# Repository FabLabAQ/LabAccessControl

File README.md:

# LabAccessControl

## FabLab access and machine control system proof-of-concept
* We use this system to manage access to our laboratory and machines usage (3D printers, laser cutter, CNC mill, etc.).
* Maker friendly and customizable, based on ESP8266 and programmed through the Arduino IDE.
* The ESP retrieves an authorized RFID cards list from a Google sheet and stores that list on flash memory, only when that list changes the internal cards list is updated with minimum flash memory wearing.
* It also logs events (what happened, when, and eventually who) on an internal FIFO and sends these logs to another Google sheet when internet connection is available.
* Due to the features above, this system can work also when internet connection goes down.

# WARNING:
Don't use MIFARE Classic cards if you don't want unauthorized access, they are clonable. Use at least Ultralight C for secure encryption.

# Development
## TODO (urgent)
Common
- [ ] diversify card keys
- [ ] switch to msgpack instead of json

Firmware
- [ ] replace DES library
- [ ] implement DES key generation
- [ ] switch to incremental mode for db updates
- [ ] implement signed messages
- [ ] implement provisioning and recovery of keys (Tang-like)

Script
- [ ] unify sheets
- [ ] incremental updates
- [ ] provisioning and recovery

App
- [ ] signed messages

## Wishlist
- [ ] switch to MQTT
- [ ] full server implmentation
- [ ] code refactoring
- [ ] external crypto chip
- [ ] smartphone nfc auth

Notes:

External crypto chip: should be used to generate card keys through hkdf/hmac, holding the source key securely and allowing it to be used only on successful authentication by the host MCU. The MCU should authenticate by recovering its private key using the procedure described above (Tang-like) or should use encrypted communications with that key.

Smartphone nfc auth: without changing the nfc reader chip (RC522), the only usable mode is host card emulation, which doesn't have a fixed UID, so the authentication protocol must be implemented on top of NDEF messages. For example: first the reader determines it's a smartphone, eventually by reading the ndef message from it, then begins the authentication process in which the reader, writing an NDEF message to the smartphone's emulated card, asks to hash some random data, and once hashed/signed using the phone's private key, that data should be read through another NDEF message and verified using the public key on the reader.

HTTP requests from Android: try retrofit

Test key: `KhGJGmHMHDS0FubbcqiVnAqxoRv1SlqD0Mg/EtXrdb0=`

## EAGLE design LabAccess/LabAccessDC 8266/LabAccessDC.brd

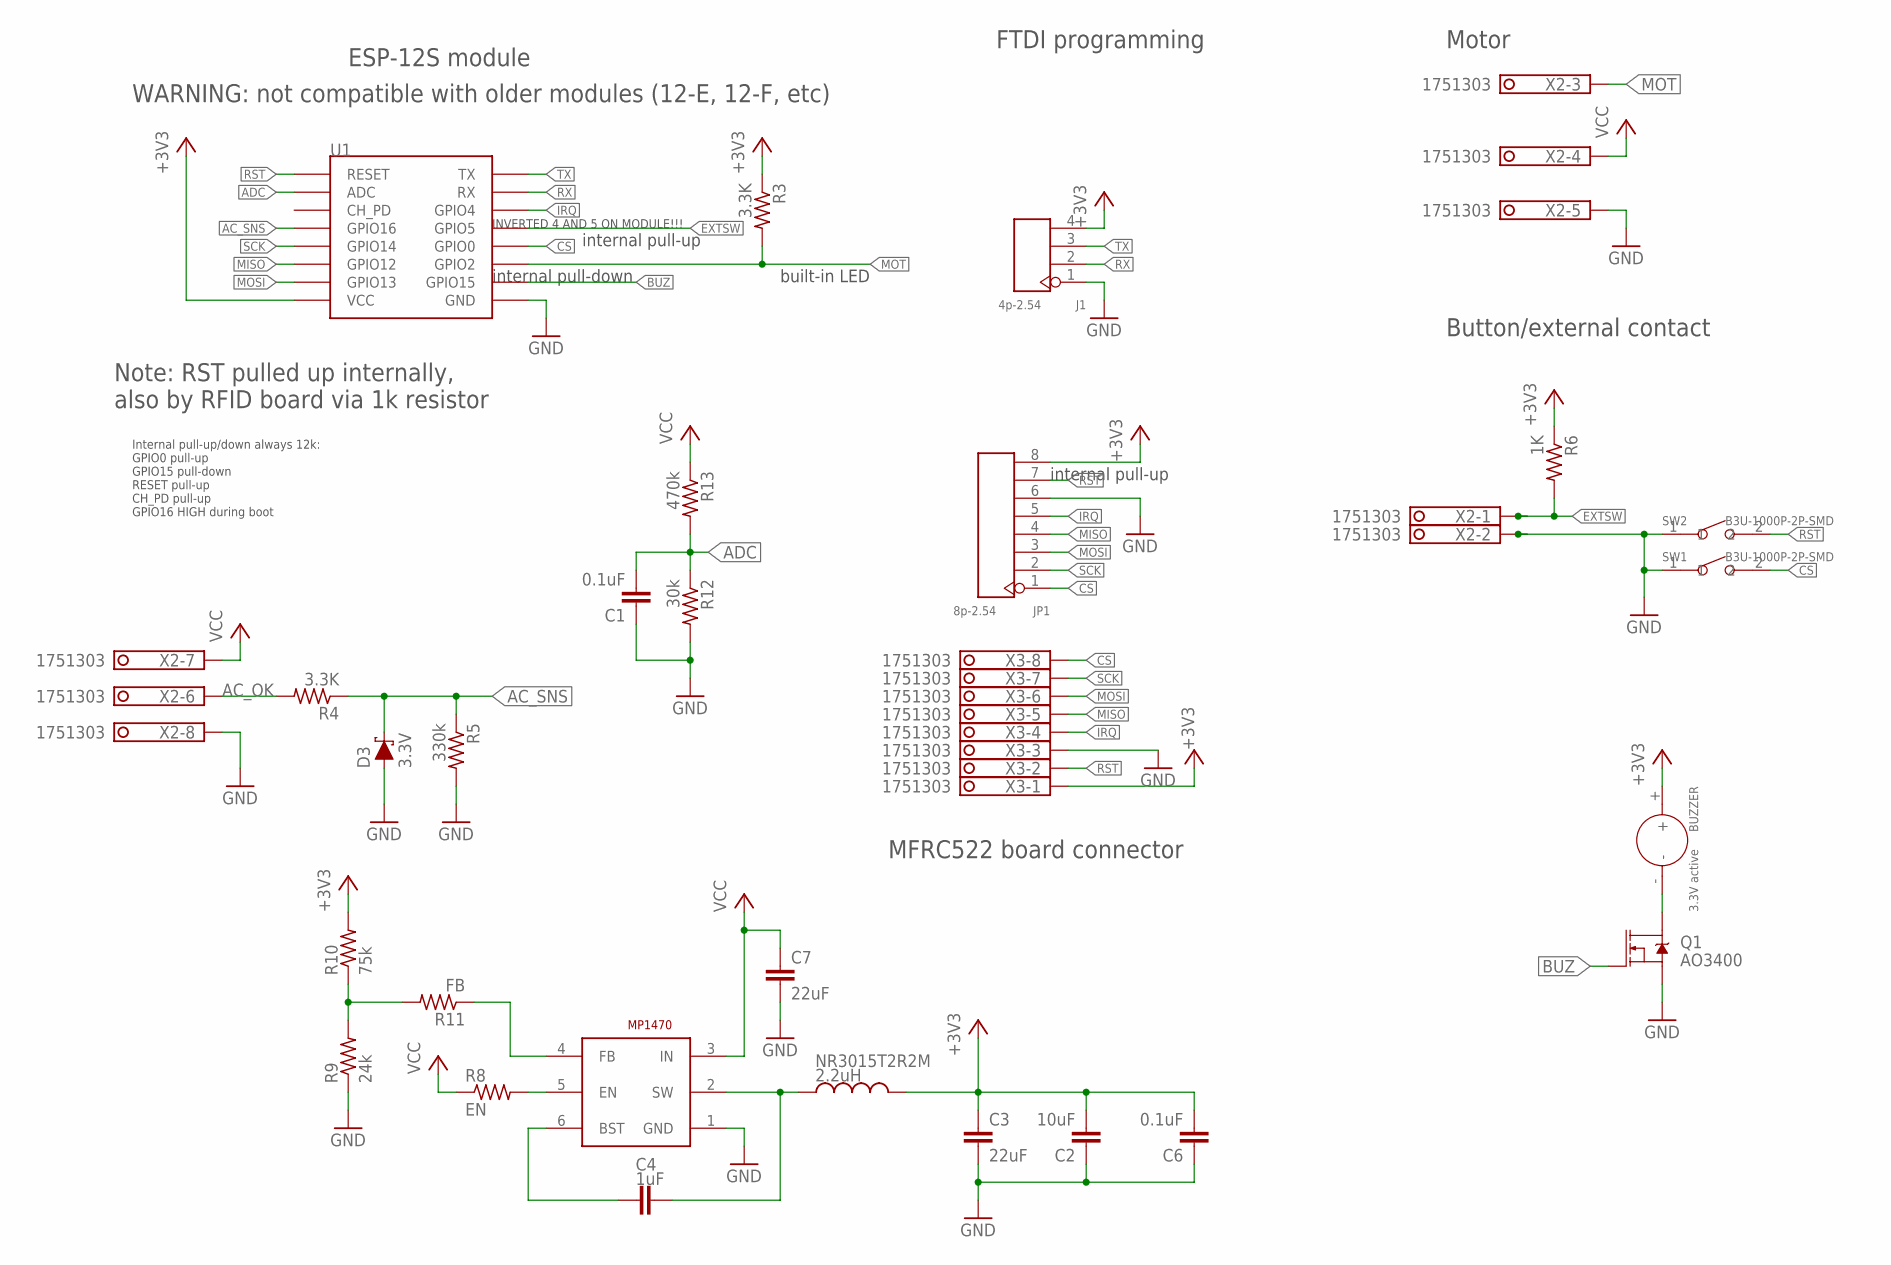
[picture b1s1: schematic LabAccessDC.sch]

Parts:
BUZZER: 3.3V active; BZ2-7.6-D12.0XH6.5MM
C1, C6: 0.1uF; C0603K
C2: 10uF; C0805K
C3, C7: 22uF; C0805K
C4: 1uF; C0603K
D3: 3.3V; SPARKFUN-DISCRETESEMI_SOD-523
J1: 4p-2.54; H4-2.54
JP1: 8p-2.54; H8-2.54
MP1470: MP1470GJ; TSOT-23-6
NR3015T2R2M: 2.2uH; INDUCTOR-NR3015
Q1: AO3400; SOT23-3
R3, R4: 3.3K; R0603
R5: 330k; R0603
R6: 1K; R0603
R8: EN; R0603
R9: 24k; R0603
R10: 75k; R0603
R11: FB; R0603
R12: 30k; R0603
R13: 470k; R0603
SW1, SW2: B3U-1000P-2P-SMD; SW2-2.6-3.0X2.5X1.2+0.4MM
U1: ESP12SMD; ESP12-SMD
X2, X3: 1751303

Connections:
+3V3: BUZZER.+, C2.2, C3.1, C6.2, J1.4, JP1.8, NR3015T2R2M.2, R3.1, R6.1, R10.2, U1.VCC, X3.1
AC_OK: R4.2, X2.6
AC_SNS: D3.C, R4.1, R5.1, U1.GPIO16
ADC: C1.2, R12.1, R13.2, U1.ADC
BUZ: Q1.1 (G), U1.GPIO15
CS: JP1.1, SW1.2, U1.GPIO0, X3.8
EXTSW: R6.2, U1.GPIO5, X2.1
GND: C1.1, C2.1, C3.2, C6.1, C7.2, D3.A, J1.1, JP1.6, MP1470.1 (GND), Q1.2 (S), R5.2, R9.1, R12.2, SW1.1, SW2.1, U1.GND, X2.2, X2.5, X2.8, X3.3
IRQ: JP1.5, U1.GPIO4, X3.4
MISO: JP1.4, U1.GPIO12, X3.5
MOSI: JP1.3, U1.GPIO13, X3.6
MOT: R3.2, U1.GPIO2, X2.3
unnamed: BUZZER.-, Q1.3 (D)
unnamed: C4.1, MP1470.6 (BST)
unnamed: C4.2, MP1470.2 (SW), NR3015T2R2M.1
unnamed: MP1470.5 (EN), R8.2
unnamed: R9.2, R10.1, R11.2
unnamed: MP1470.4 (FB), R11.1
RST: JP1.7, SW2.2, U1.RESET, X3.2
RX: J1.2, U1.RXD0 (RX)
SCK: JP1.2, U1.GPIO14, X3.7
TX: J1.3, U1.TXD0 (TX)
VCC: C7.1, MP1470.3 (IN), R8.1, R13.1, X2.4, X2.7

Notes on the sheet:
ESP-12S module
Note: RST pulled up internally, also by RFID board via 1k resistor
FTDI programming
Button/external contact
MFRC522 board connector
built-in LED
internal pull-down
internal pull-up
INVERTED 4 AND 5 ON MODULE!!!
Internal pull-up/down always 12k: GPIO0 pull-up GPIO15 pull-down RESET pull-up CH_PD pull-up GPIO16 HIGH during boot
Motor
WARNING: not compatible with older modules (12-E, 12-F, etc)

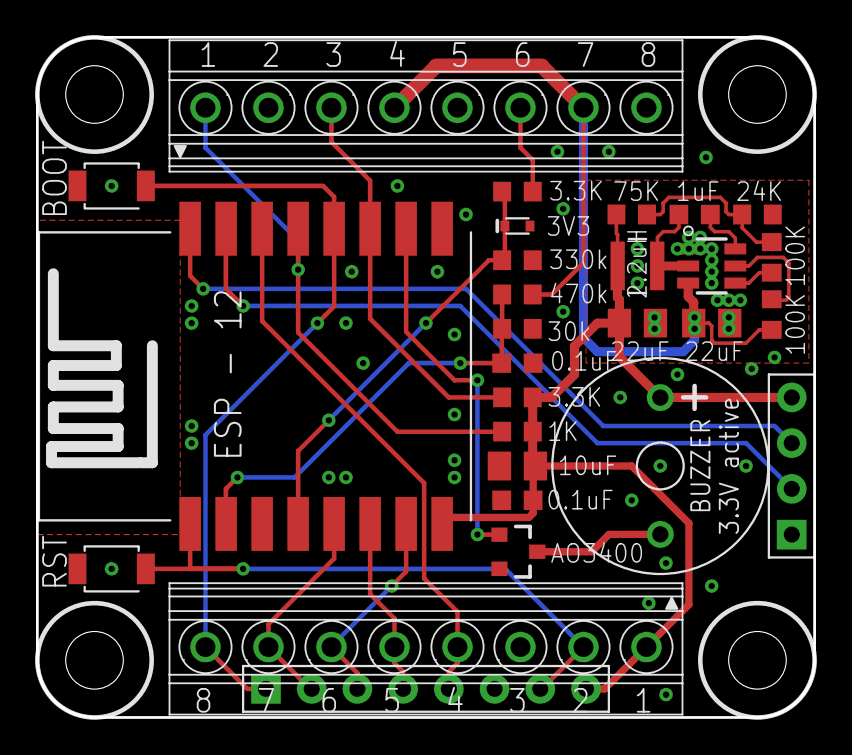
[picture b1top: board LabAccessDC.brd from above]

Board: 2 copper layers, 43.2 x 37.8 mm, 29 parts (1 on the bottom side), 23 nets.

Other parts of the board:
U$3: OSHW-LOGO-L

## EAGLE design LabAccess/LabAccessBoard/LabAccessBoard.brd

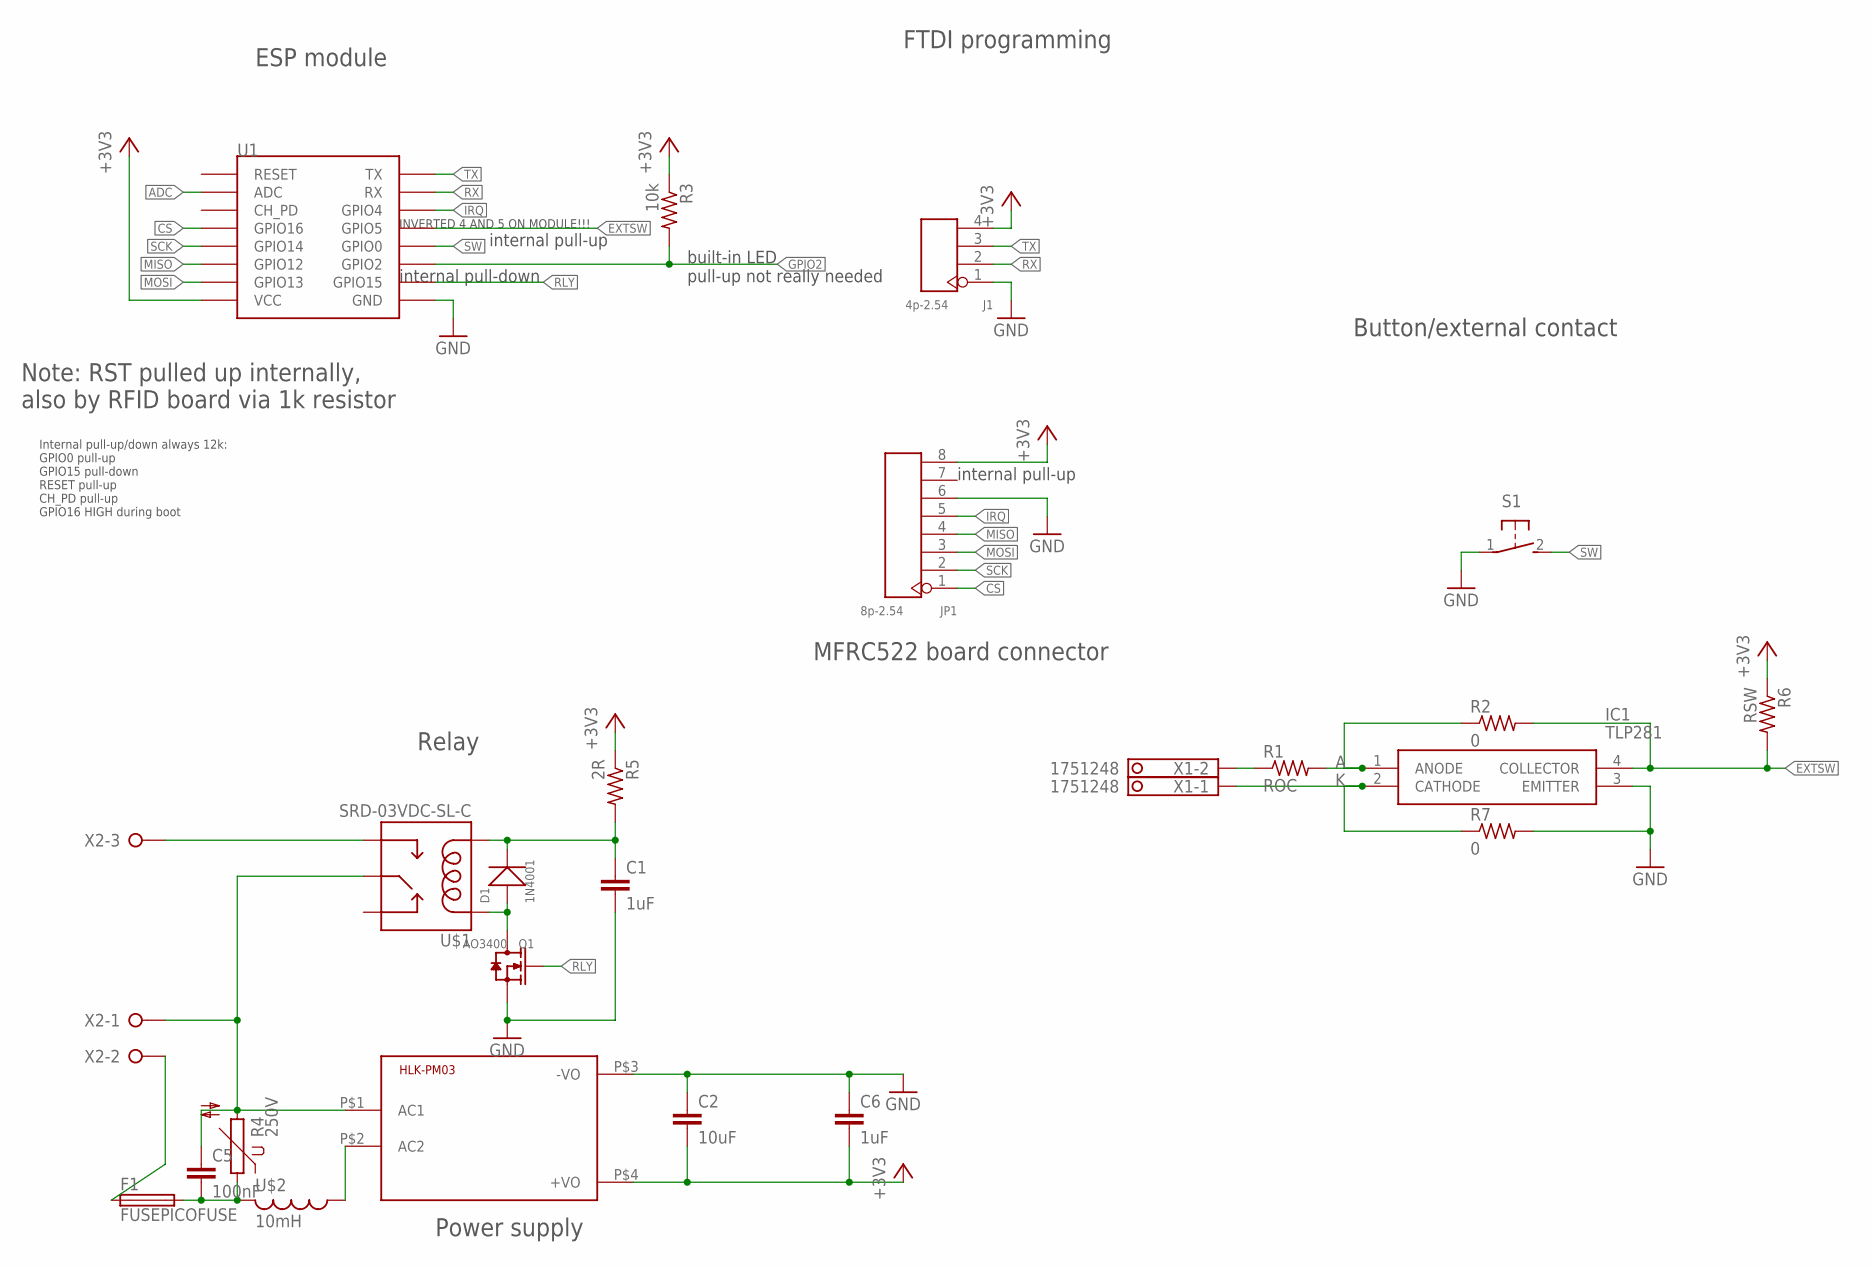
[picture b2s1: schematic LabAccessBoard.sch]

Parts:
C1, C6: 1uF; C0603K
C2: 10uF; C0805K
C5: 100nF; C102-064X133
D1: 1N4001; DO-214AC
F1: FUSEPICOFUSE; PICOFUSE
HLK-PM03: HLK-PM03; HLK-PM01
IC1: TLP281; SOIC127P700X190-4N
J1: 4p-2.54; H4-2.54
JP1: 8p-2.54; H8-2.54
Q1: AO3400; SOT-23
R1: ROC; R0603
R2, R7: 0; R0603
R3: 10k; R0603
R4: 250V; S07K250
R5: 2R; R0603
R6: RSW; R0603
S1: 31-XX; B3F-31XX
U1: ESP12SMD; ESP12-SMD
U$1: SRD-03VDC-SL-C; SRD-0XVDC-SL-C
U$2: 10mH; 6000-XXXX-RC
X1: 1751248
X2: W237-3E

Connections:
+3V3: C2.2, C6.2, HLK-PM03.P$4 (+VO), J1.4, JP1.8, R3.1, R5.1, R6.1, U1.VCC
A: IC1.1 (ANODE), R1.2, R2.1
ADC: U1.ADC
CS: JP1.1, U1.GPIO16
EXTSW: IC1.4 (COLLECTOR), R2.2, R6.2, U1.GPIO5
GND: C1.2, C2.1, C6.1, HLK-PM03.P$3 (-VO), IC1.3 (EMITTER), J1.1, JP1.6, Q1.2 (S), R7.2, S1.1, U1.GND
GPIO2: R3.2, U1.GPIO2
IRQ: JP1.5, U1.GPIO4
K: IC1.2 (CATHODE), R7.1, X1.1
MISO: JP1.4, U1.GPIO12
MOSI: JP1.3, U1.GPIO13
unnamed: U$1.SWOPEN, X2.3
unnamed: C5.1, HLK-PM03.P$1 (AC1), R4.2, U$1.SWCOMMON, X2.1
unnamed: C5.2, F1.2, R4.1, U$2.2
unnamed: F1.1, X2.2
unnamed: C1.1, D1.2 (-), R5.2, U$1.COIL0
unnamed: HLK-PM03.P$2 (AC2), U$2.1
unnamed: D1.1 (+), Q1.3 (D), U$1.COIL1
unnamed: R1.1, X1.2
RLY: Q1.1 (G), U1.GPIO15
RX: J1.2, U1.RXD0 (RX)
SCK: JP1.2, U1.GPIO14
SW: S1.2 (S), U1.GPIO0
TX: J1.3, U1.TXD0 (TX)

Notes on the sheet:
ESP module
Note: RST pulled up internally, also by RFID board via 1k resistor
FTDI programming
Button/external contact
MFRC522 board connector
Power supply
Relay
built-in LED pull-up not really needed
internal pull-down
internal pull-up
INVERTED 4 AND 5 ON MODULE!!!
Internal pull-up/down always 12k: GPIO0 pull-up GPIO15 pull-down RESET pull-up CH_PD pull-up GPIO16 HIGH during boot

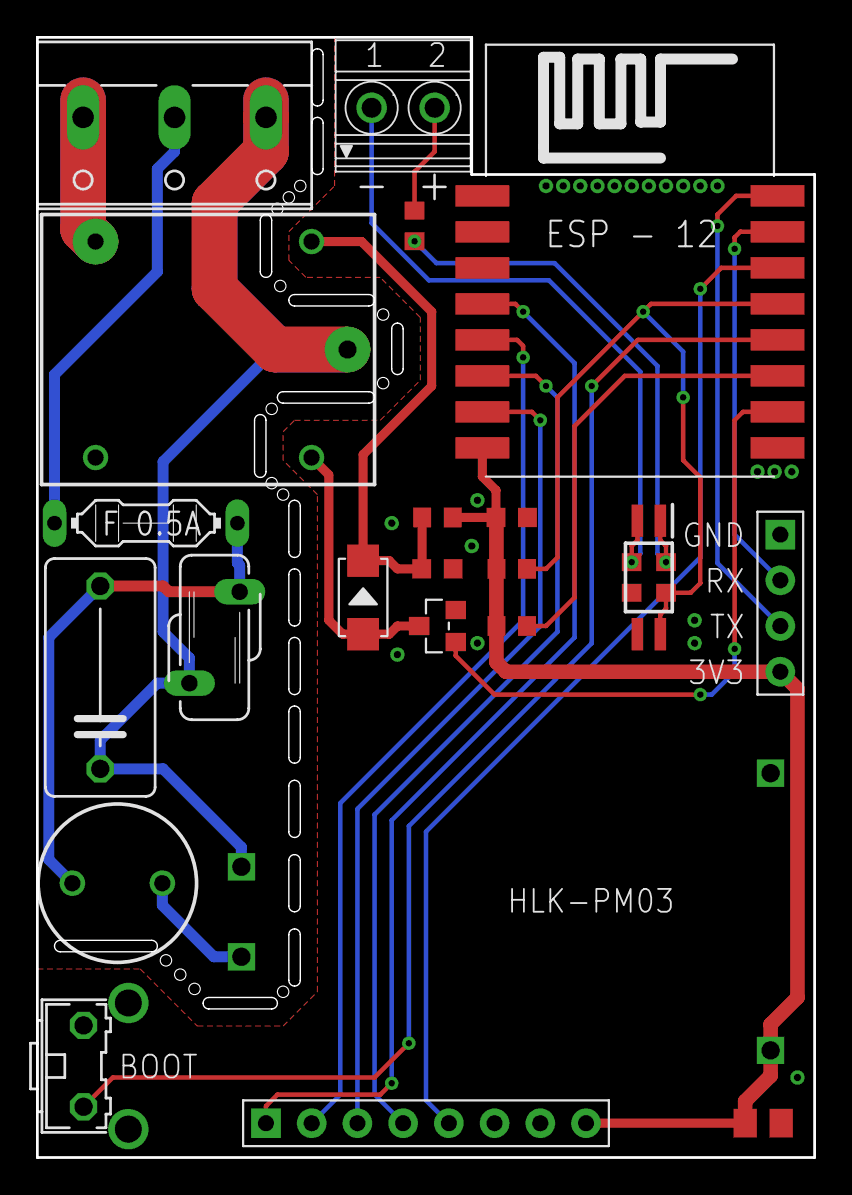
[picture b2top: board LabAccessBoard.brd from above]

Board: 2 copper layers, 43.2 x 62.2 mm, 25 parts (1 on the bottom side), 23 nets.

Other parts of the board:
U$3: OSHW-LOGO-L

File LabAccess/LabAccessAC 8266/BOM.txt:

Minimum setup:
1x ESP-12 module
1x HLK-PM03 power supply
1x SRD-03VDC-SL-C relay
1x 0805 22uF 25V ceramic capacitors
2x 0603 1uF 25V ceramic capacitors
1x 07D391K 7mm 250Vrms varistor
1x 100nF 10mm pitch X2 rated capacitor
1x 10mH 8x10mm inductor (few mA)
1x 500mA 250V axial fuse
1x 1N400x SOD-323 diode or equivalent
1x AO3400 SOT23-3 N-MOSFET or equivalent
1x 0603 2ohm resistor
1x 0603 10k resistor
1x 8p 2.54mm female header
1x 4p 2.54mm male header (or pogo-pins)
1x 3p 5.08mm screw terminal
1x horizontal button

Optional for external switch:
1x 3.5mm 2p screw terminal
3x 0603 0ohm resistors (one marked ROC, two in place of TLP281)
1x 0603 pull-up resistor depending on environment (marked RSW)

Optional for optocoupler setup:
1x TLP281
1x 0603 series resistor depending on input voltage (marked ROC)
1x 0603 pull-up resistor around 1k (marked RSW)

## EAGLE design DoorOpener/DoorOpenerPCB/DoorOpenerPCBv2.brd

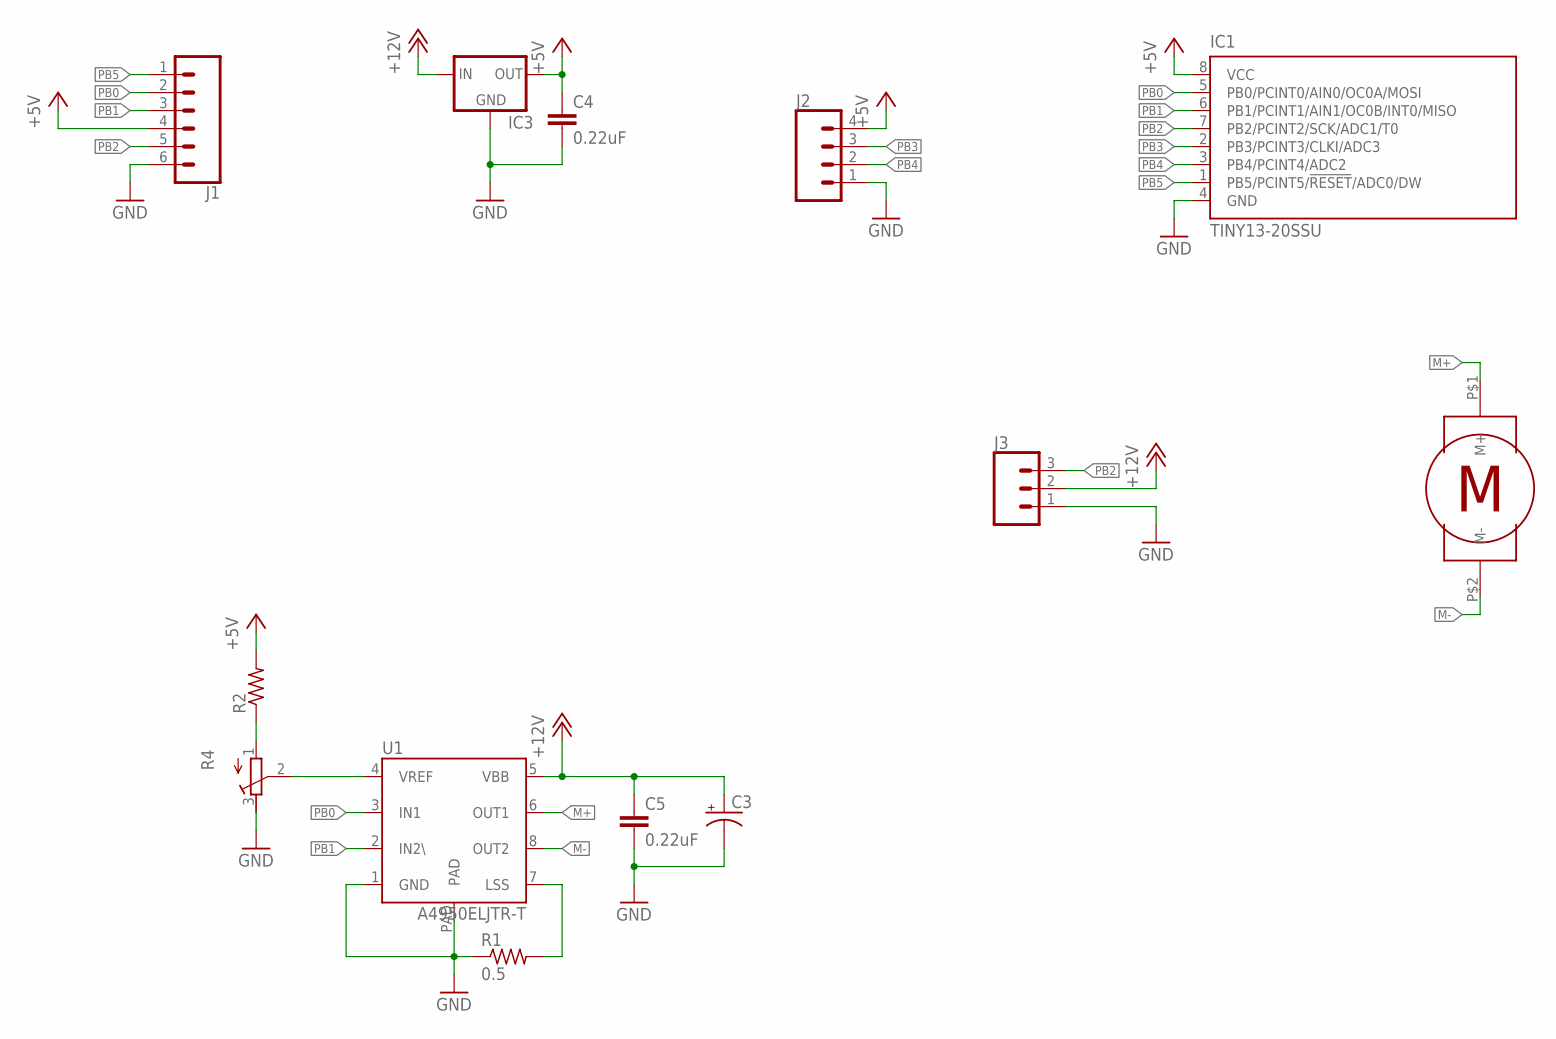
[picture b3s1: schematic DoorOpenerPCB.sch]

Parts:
C3: CPOL-USCT3528; CT3528
C4, C5: 0.22uF; C0603K
IC1: TINY13-20SSU; 8S1
IC3: 78LXX-SOT89R; SOT89R
J1: CONN_061.27MM; 1X06_1.27MM
J2: CONN_041.27MM; 1X04_1.27MM
J3: CONN_03JST-PTH-NS; JST-3-PTH-NS
R1: 0.5; R0805
R2: R-US_R0603; R0603
R4: R-TRIMM3103; RTRIM3103
U1: A4950ELJTR-T; SOIC8TP
U$2: JGY-370; PKG

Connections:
+5V: C4.1, IC1.8 (VCC), IC3.2 (OUT), J1.4, J2.4, R2.2
+12V: C3.+, C5.1, IC3.1 (IN), J3.2, U1.5 (VBB)
GND: C3.-, C4.2, C5.2, IC1.4 (GND), IC3.3 (GND), IC3.4 (GND), J1.6, J2.1, J3.1, R1.1, R4.3 (E), U1.1 (GND), U1.PAD
M+: U1.6 (OUT1), U$2.P$1 (M+)
M-: U1.8 (OUT2), U$2.P$2 (M-)
unnamed: R4.2 (S), U1.4 (VREF)
unnamed: R1.2, U1.7 (LSS)
unnamed: R2.1, R4.1 (A)
PB0: IC1.5 (PB0/PCINT0/AIN0/OC0A/MOSI), J1.2, U1.3 (IN1)
PB1: IC1.6 (PB1/PCINT1/AIN1/OC0B/INT0/MISO), J1.3, U1.2 (IN2\)
PB2: IC1.7 (PB2/PCINT2/SCK/ADC1/T0), J1.5, J3.3
PB3: IC1.2 (PB3/PCINT3/CLKI/ADC3), J2.3
PB4: IC1.3 (PB4/PCINT4/ADC2), J2.2
PB5: IC1.1 (PB5/PCINT5/!RESET!/ADC0/DW), J1.1

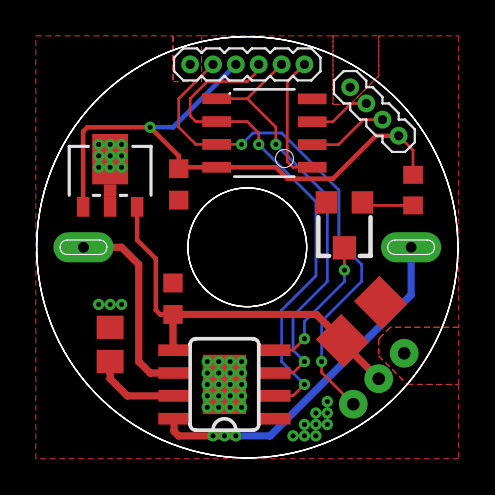
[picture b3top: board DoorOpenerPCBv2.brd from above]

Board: 2 copper layers, 23.4 x 23.4 mm, 13 parts (0 on the bottom side), 14 nets.

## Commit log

2018-05-30 AccessControlBoard
2018-06-02 CardMakerFW
2018-06-19 board release candidate
2018-06-21 started firmware development
2018-07-05 first release
2018-07-20 communication protocol update
2018-08-23 first woking version
2018-08-30 added license
2018-09-04 new folder structure
2018-09-22 pot board
2018-10-07 board update
2018-11-07 pin assignment
2018-12-08 new lab access board
2018-12-08 lab access board DC
2019-01-24 management scripts
2019-01-30 Started new version development
2019-01-30 cleanup
2019-01-31 small fix
2022-01-13 platformio project
2022-01-18 new update and config process
2022-12-15 road to 0.2
2023-01-12 various updates

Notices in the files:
LabAccess/LabAccessBoard/LabAccessBoard.brd:
(c)2018 Luca Anastasio
parts and their libraries:
SparkFun-Connectors: Licensing: Creative Commons ShareAlike 4.0 International - https://creativecommons.org/licenses/by-sa/4.0
